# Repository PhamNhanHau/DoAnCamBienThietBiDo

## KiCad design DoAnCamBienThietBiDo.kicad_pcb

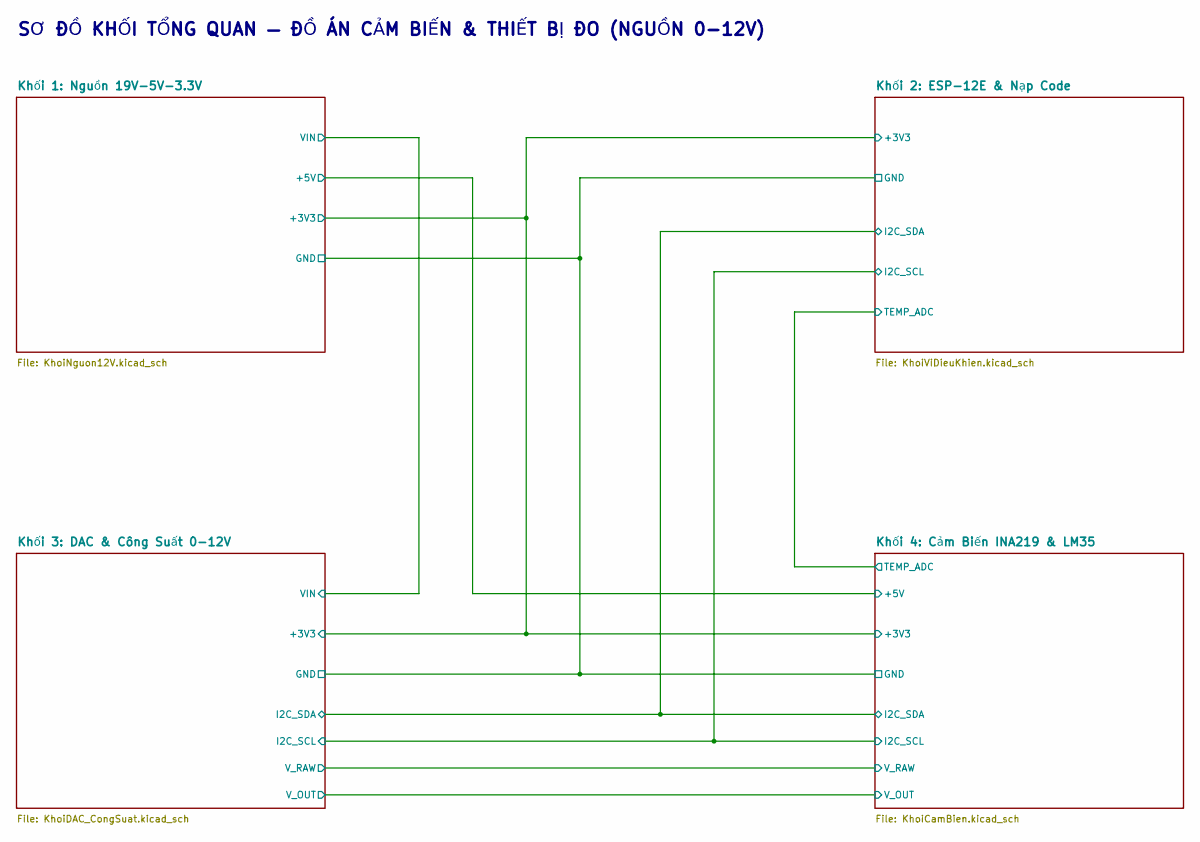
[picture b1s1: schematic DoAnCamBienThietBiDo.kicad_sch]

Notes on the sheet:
SƠ ĐỒ KHỐI TỔNG QUAN — ĐỒ ÁN CẢM BIẾN & THIẾT BỊ ĐO (NGUỒN 0-12V)

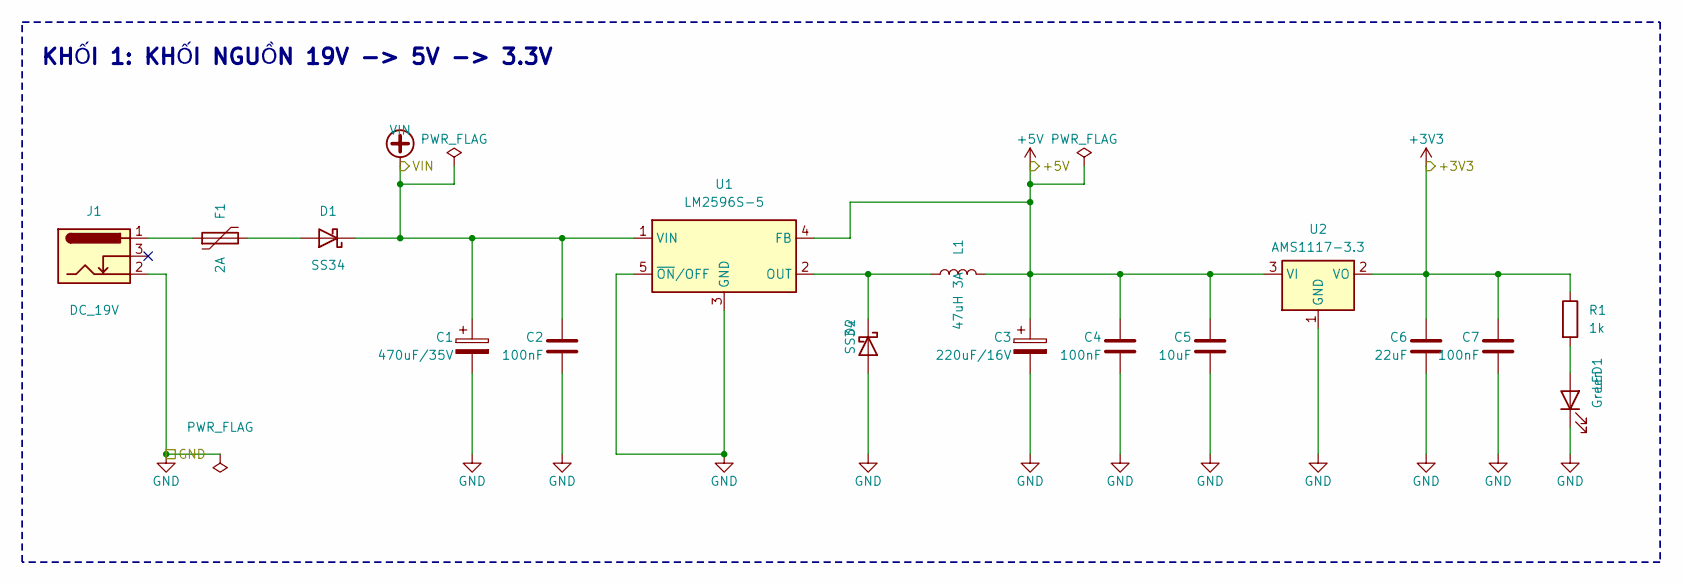
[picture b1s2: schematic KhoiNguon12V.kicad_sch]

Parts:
C1: 470uF/35V; CP_Radial_D10.0mm_P5.00mm
C2, C4, C7: 100nF; C_0805_2012Metric
C3: 220uF/16V; CP_Radial_D8.0mm_P3.50mm
C5: 10uF; C_0805_2012Metric
C6: 22uF; C_0805_2012Metric
D1, D2: SS34; D_SMA
F1: 2A; Fuse_1812_4532Metric
J1: DC_19V; BarrelJack_Horizontal
L1: 47uH 3A; L_12x12mm_H6mm
LED1: Green; LED_0805_2012Metric
R1: 1k; R_0805_2012Metric
U1: LM2596S-5; TO-263-5_TabPin3
U2: AMS1117-3.3; SOT-223-3_TabPin2

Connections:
+3V3: C6.1, C7.1, R1.1, U2.2 (VO); also elsewhere on the board
+5V: C3.1, C4.1, C5.1, L1.2, U1.4 (FB), U2.3 (VI); also elsewhere on the board
GND: C1.2, C2.2, C3.2, C4.2, C5.2, C6.2, C7.2, D2.2 (A), J1.2, LED1.1 (K), U1.3 (GND), U1.5 (~ON/OFF), U2.1 (GND); also elsewhere on the board
unnamed: D1.2 (A), F1.2
unnamed: D2.1 (K), L1.1, U1.2 (OUT)
unnamed: F1.1, J1.1
unnamed: LED1.2 (A), R1.2
VIN: C1.1, C2.1, D1.1 (K), U1.1 (VIN); also elsewhere on the board

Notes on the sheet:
KHỐI 1: KHỐI NGUỒN 19V -> 5V -> 3.3V

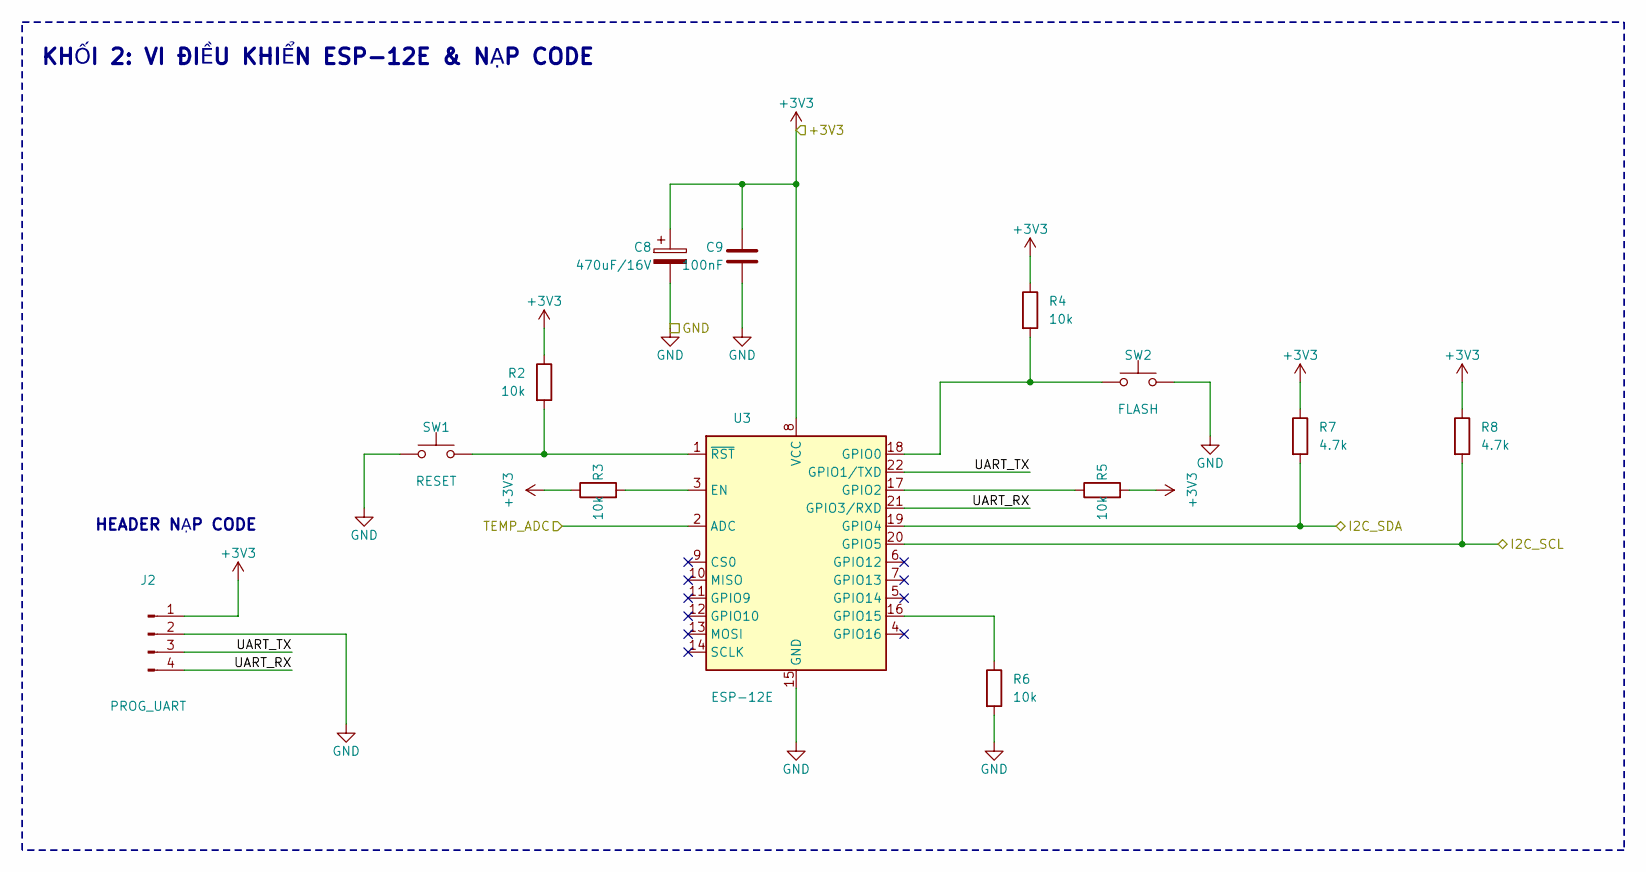
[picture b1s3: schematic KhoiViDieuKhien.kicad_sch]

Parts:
C8: 470uF/16V; CP_Radial_D8.0mm_P3.50mm
C9: 100nF; C_0805_2012Metric
J2: PROG_UART; PinHeader_1x04_P2.54mm_Vertical
R2, R3, R4, R5, R6: 10k; R_0805_2012Metric
R7, R8: 4.7k; R_0805_2012Metric
SW1: RESET; SW_SPST_CK_RS282G05A3
SW2: FLASH; SW_SPST_CK_RS282G05A3
U3: ESP-12E

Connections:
+3V3: C8.1, C9.1, J2.1, R2.1, R3.1, R4.1, R5.2, R7.1, R8.1, U3.8 (VCC); also elsewhere on the board
/Khối 2: ESP-12E & Nạp Code/I2C_SCL: R8.2, U3.20 (GPIO5); also elsewhere on the board
/Khối 2: ESP-12E & Nạp Code/I2C_SDA: R7.2, U3.19 (GPIO4); also elsewhere on the board
/Khối 2: ESP-12E & Nạp Code/TEMP_ADC: U3.2 (ADC); also elsewhere on the board
/Khối 2: ESP-12E & Nạp Code/UART_RX: J2.4, U3.21 (GPIO3/RXD)
/Khối 2: ESP-12E & Nạp Code/UART_TX: J2.3, U3.22 (GPIO1/TXD)
GND: C8.2, C9.2, J2.2, R6.2, SW1.1, SW2.2, U3.15 (GND); also elsewhere on the board
unnamed: R3.2, U3.3 (EN)
unnamed: R4.2, SW2.1, U3.18 (GPIO0)
unnamed: R5.1, U3.17 (GPIO2)
unnamed: R6.1, U3.16 (GPIO15)
unnamed: R2.2, SW1.2, U3.1 (~RST)

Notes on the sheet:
KHỐI 2: VI ĐIỀU KHIỂN ESP-12E & NẠP CODE
HEADER NẠP CODE

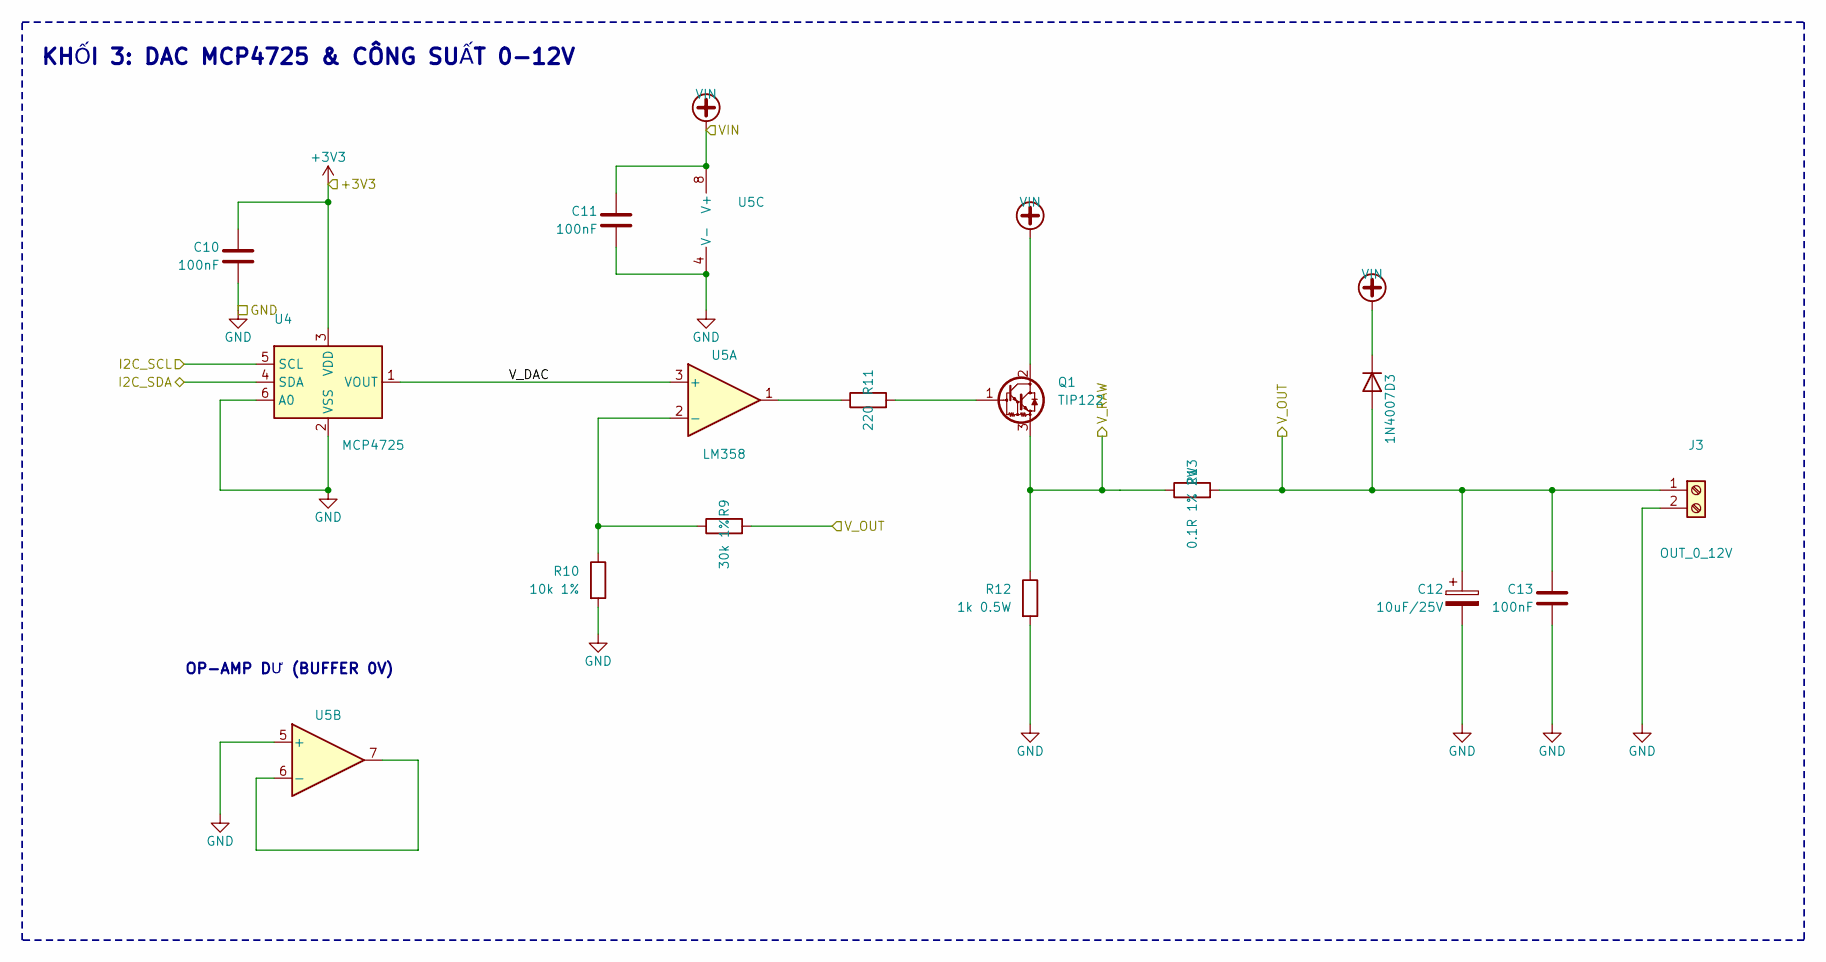
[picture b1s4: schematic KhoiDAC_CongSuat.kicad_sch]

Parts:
C10, C11, C13: 100nF; C_0805_2012Metric
C12: 10uF/25V; CP_Radial_D5.0mm_P2.00mm
D3: 1N4007; D_DO-41_SOD81_P10.16mm_Horizontal
J3: OUT_0_12V; TerminalBlock_Phoenix_MKDS-1,5-2-5.08_1x02_P5.08mm_Horizont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
Q1: TIP122; TO-220-3_Vertical
R9: 30k 1%; R_0805_2012Metric
R10: 10k 1%; R_0805_2012Metric
R11: 220; R_0805_2012Metric
R12: 1k 0.5W; R_0805_2012Metric
R13: 0.1R 1% 2W; R_2512_6332Metric
U4: MCP4725; SOT-23-6
U5: LM358; SOIC-8_3.9x4.9mm_P1.27mm

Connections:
+3V3: C10.1, U4.3 (VDD); also elsewhere on the board
/Khối 2: ESP-12E & Nạp Code/I2C_SCL: U4.5 (SCL); also elsewhere on the board
/Khối 2: ESP-12E & Nạp Code/I2C_SDA: U4.4 (SDA); also elsewhere on the board
/Khối 3: DAC & Công Suất 0-12V/V_DAC: U4.1 (VOUT), U5.3 (+)
/Khối 3: DAC & Công Suất 0-12V/V_OUT: C12.1, C13.1, D3.2 (A), J3.1, R9.2, R13.2; also elsewhere on the board
/Khối 3: DAC & Công Suất 0-12V/V_RAW: Q1.3 (E), R12.1, R13.1; also elsewhere on the board
GND: C10.2, C11.2, C12.2, C13.2, J3.2, R10.2, R12.2, U4.2 (VSS), U4.6 (A0), U5.4 (V-), U5.5 (+); also elsewhere on the board
unnamed: Q1.1 (B), R11.2
unnamed: R11.1, U5.1
unnamed: R9.1, R10.1, U5.2 (-)
unnamed: U5.6 (-), U5.7
VIN: C11.1, D3.1 (K), Q1.2 (C), U5.8 (V+); also elsewhere on the board

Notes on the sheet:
KHỐI 3: DAC MCP4725 & CÔNG SUẤT 0-12V
OP-AMP DƯ (BUFFER 0V)

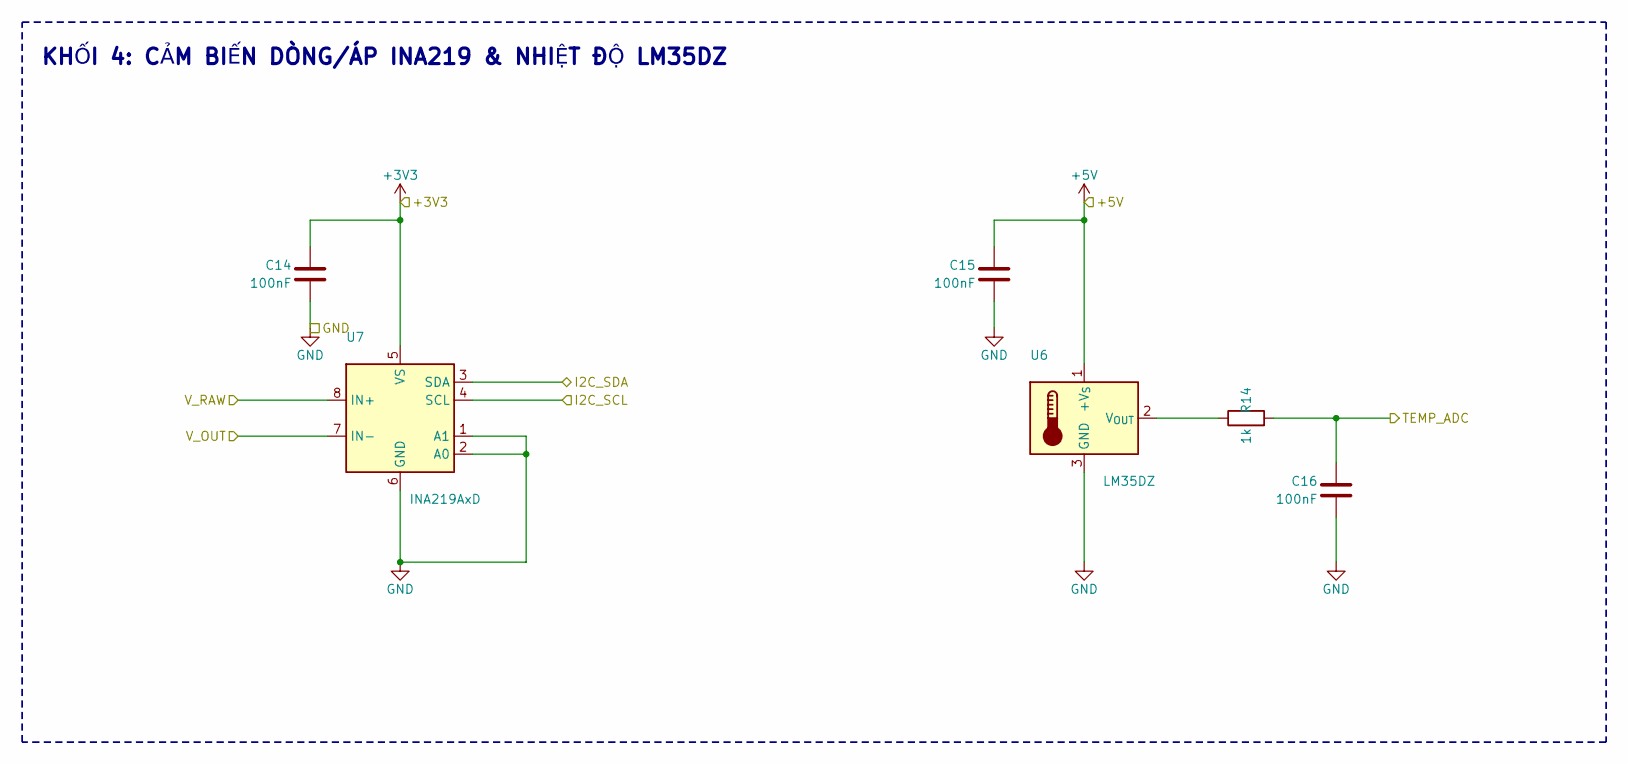
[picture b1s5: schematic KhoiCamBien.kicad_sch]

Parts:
C14, C15, C16: 100nF; C_0805_2012Metric
R14: 1k; R_0805_2012Metric
U6: LM35DZ; TO-92_Inline
U7: INA219AxD; SOIC-8_3.9x4.9mm_P1.27mm

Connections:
+3V3: C14.1, U7.5 (VS); also elsewhere on the board
+5V: C15.1, U6.1 (+V_{S}); also elsewhere on the board
/Khối 2: ESP-12E & Nạp Code/I2C_SCL: U7.4 (SCL); also elsewhere on the board
/Khối 2: ESP-12E & Nạp Code/I2C_SDA: U7.3 (SDA); also elsewhere on the board
/Khối 2: ESP-12E & Nạp Code/TEMP_ADC: C16.1, R14.2; also elsewhere on the board
/Khối 3: DAC & Công Suất 0-12V/V_OUT: U7.7 (IN-); also elsewhere on the board
/Khối 3: DAC & Công Suất 0-12V/V_RAW: U7.8 (IN+); also elsewhere on the board
GND: C14.2, C15.2, C16.2, U6.3 (GND), U7.1 (A1), U7.2 (A0), U7.6 (GND); also elsewhere on the board
unnamed: R14.1, U6.2 (V_{OUT})

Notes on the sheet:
KHỐI 4: CẢM BIẾN DÒNG/ÁP INA219 & NHIỆT ĐỘ LM35DZ

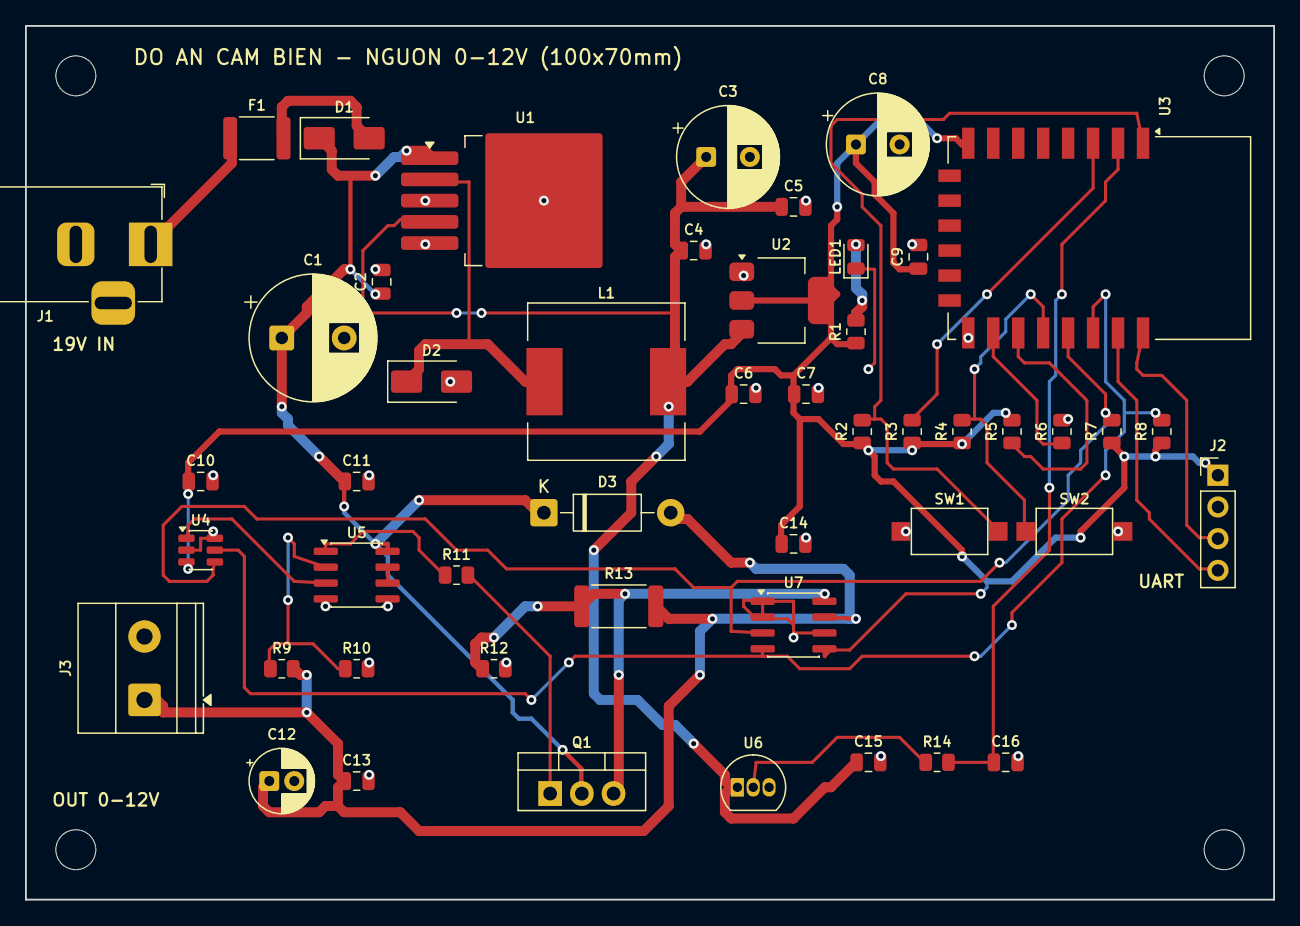
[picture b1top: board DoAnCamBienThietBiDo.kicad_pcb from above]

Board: 2 copper layers, 100.0 x 70.0 mm, 53 parts (0 on the bottom side), 26 nets.

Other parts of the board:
H1, H2, H3, H4: M3; MountingHole_3.2mm_M3
